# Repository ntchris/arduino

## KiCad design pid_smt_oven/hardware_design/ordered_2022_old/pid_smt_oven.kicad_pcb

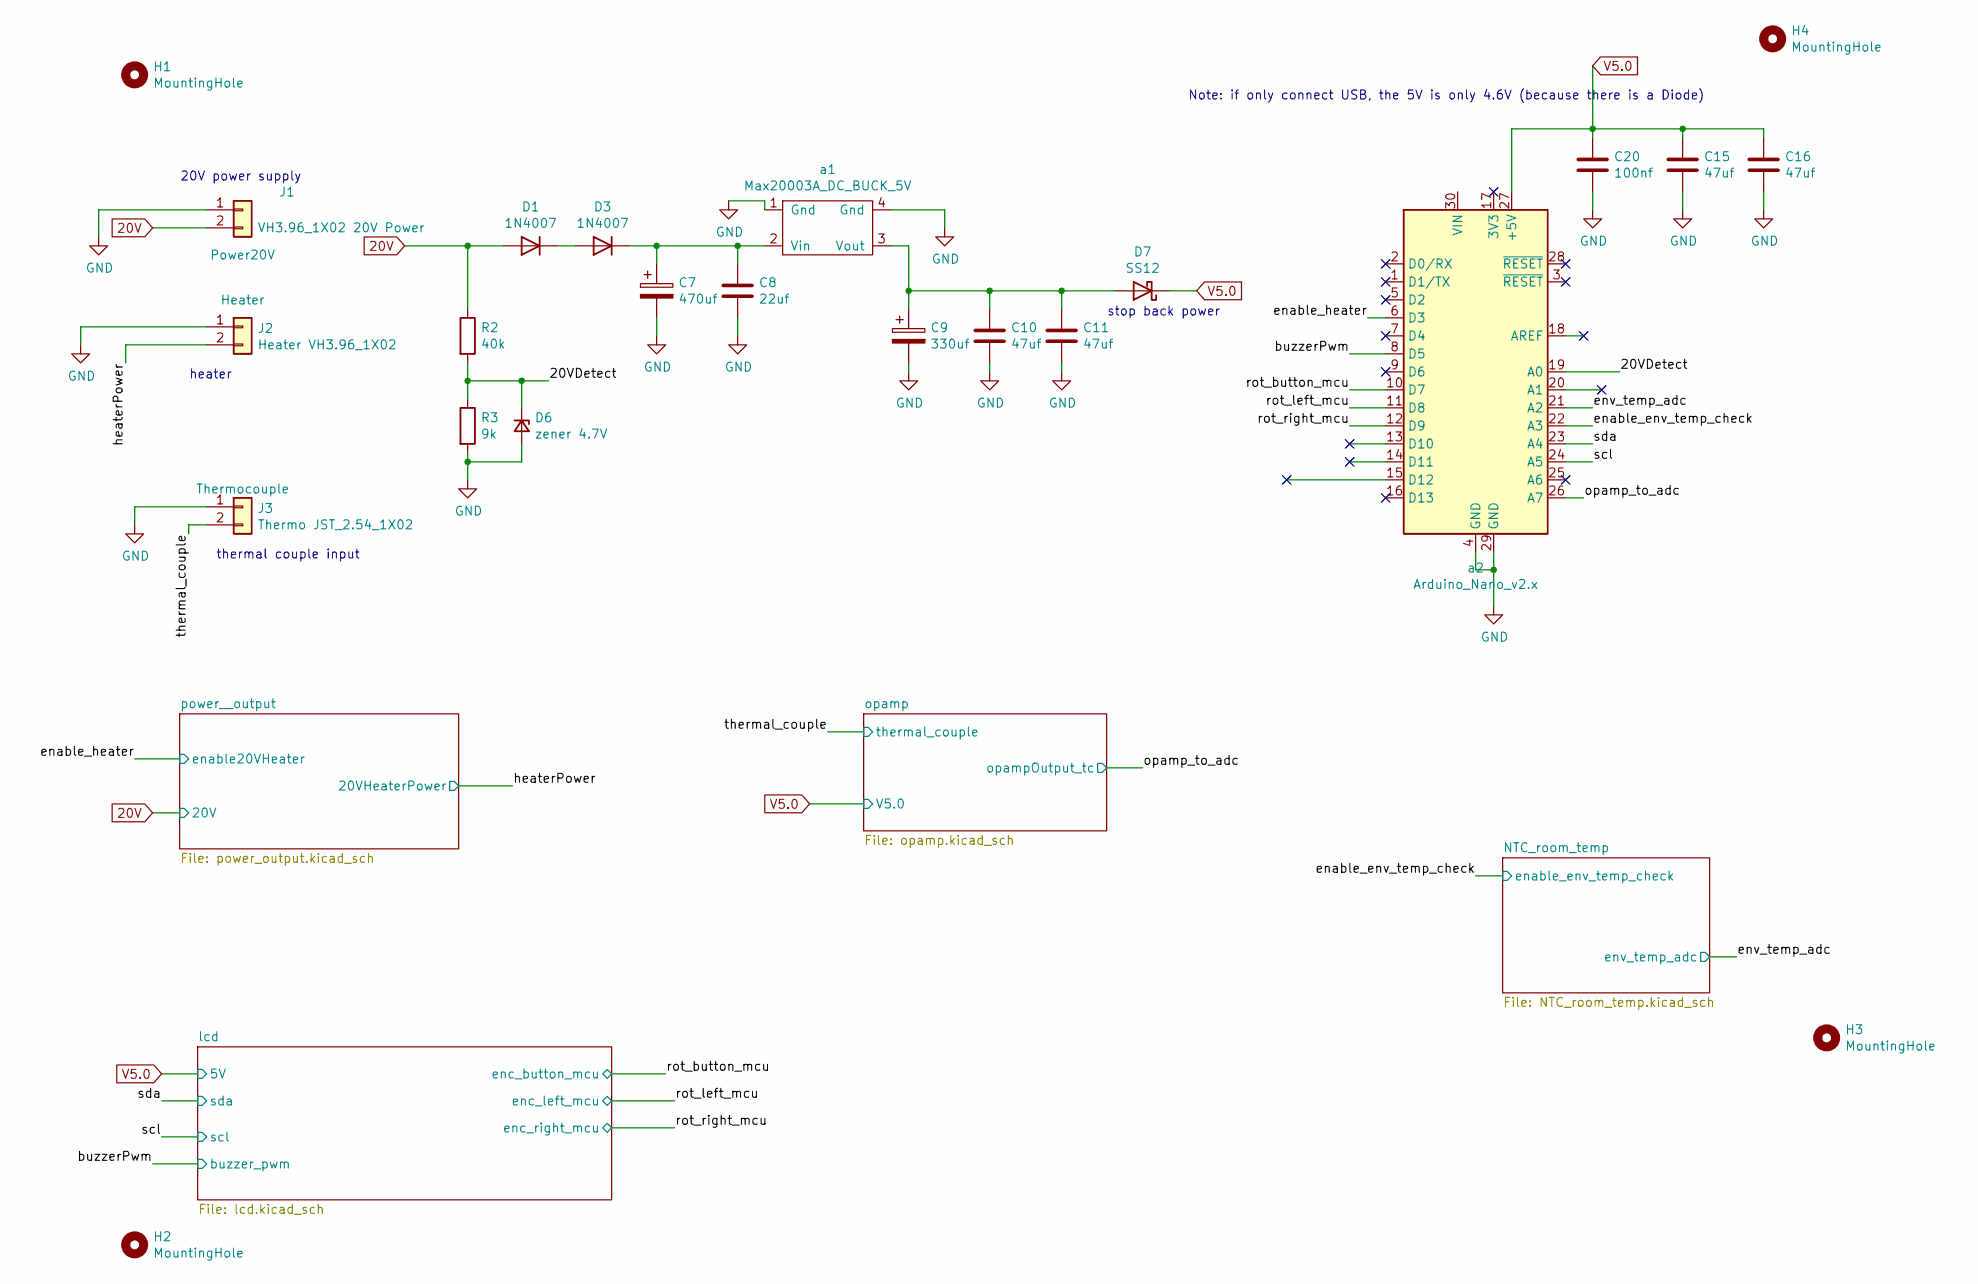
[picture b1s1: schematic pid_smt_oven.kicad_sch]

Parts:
C7: 470uf; CP_Radial_D8.0mm_P3.80mm
C8: 22uf; C_1206_3216Metric_Pad1.33x1.80mm_HandSolder
C9: 330uf; CP_EIA-7343-20_Kemet-V_Pad2.25x2.55mm_HandSolder
C10, C11, C15, C16: 47uf; R_C_0805_2012Metric_Pad1.20x1.50mm_HandSolder
C20: 100nf; R_C_0805_2012Metric_Pad1.20x1.50mm_HandSolder
D1, D3: 1N4007; D_SMA_Handsoldering
D6: zener 4.7V; D_MiniMELF_Handsoldering_Zener
D7: SS12; D_SMA_Handsoldering
H1, H2, H3, H4: MountingHole; MountingHole_2.0mm
J1: VH3.96_1X02 20V Power; JST_VH_B2P-VH-B_1x02_P3.96mm_Vertical
J2: Heater VH3.96_1X02; JST_VH_B2P-VH-B_1x02_P3.96mm_Vertical
J3: Thermo JST_2.54_1X02; Molex_KK-254_AE-6410-02A_1x02_P2.54mm_Vertical
R2: 40k; R_C_0805_2012Metric_Pad1.20x1.50mm_HandSolder
R3: 9k; R_C_0805_2012Metric_Pad1.20x1.50mm_HandSolder
a1: Max20003A_DC_BUCK_5V; MAX20003A_dc_buck_module
a2: Arduino_Nano_v2.x; Arduino_Nano_order

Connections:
20V: D1.2 (A), J1.2, R2.1; also elsewhere on the board
/20VDetect: D6.1 (K), R2.2, R3.1, a2.19 (A0)
/buzzerPwm: a2.8 (D5); also elsewhere on the board
/enable_env_temp_check: a2.22 (A3); also elsewhere on the board
/enable_heater: a2.6 (D3); also elsewhere on the board
/env_temp_adc: a2.21 (A2); also elsewhere on the board
/heaterPower: J2.2; also elsewhere on the board
/opamp_to_adc: a2.26 (A7); also elsewhere on the board
/relayTrigger: a2.15 (D12)
/rot_button_mcu: a2.10 (D7); also elsewhere on the board
/rot_left_mcu: a2.11 (D8); also elsewhere on the board
/rot_right_mcu: a2.12 (D9); also elsewhere on the board
/scl: a2.24 (A5); also elsewhere on the board
/sda: a2.23 (A4); also elsewhere on the board
/thermal_couple: J3.2; also elsewhere on the board
GND: C7.2, C8.2, C9.2, C10.2, C11.2, C15.2, C16.2, C20.2, D6.2 (A), J1.1, J2.1, J3.1, R3.2, a1.1 (Gnd), a1.4 (Gnd), a2.4 (GND), a2.29 (GND); also elsewhere on the board
unnamed: C7.1, C8.1, D3.1 (K), a1.2 (Vin)
unnamed: C9.1, C10.1, C11.1, D7.2 (A), a1.3 (Vout)
unnamed: D1.1 (K), D3.2 (A)
V5.0: C15.1, C16.1, C20.1, D7.1 (K), a2.27 (+5V); also elsewhere on the board

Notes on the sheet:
heater
stop back power
20V power supply
thermal couple input
Note: if only connect USB, the 5V is only 4.6V (because there is a Diode)

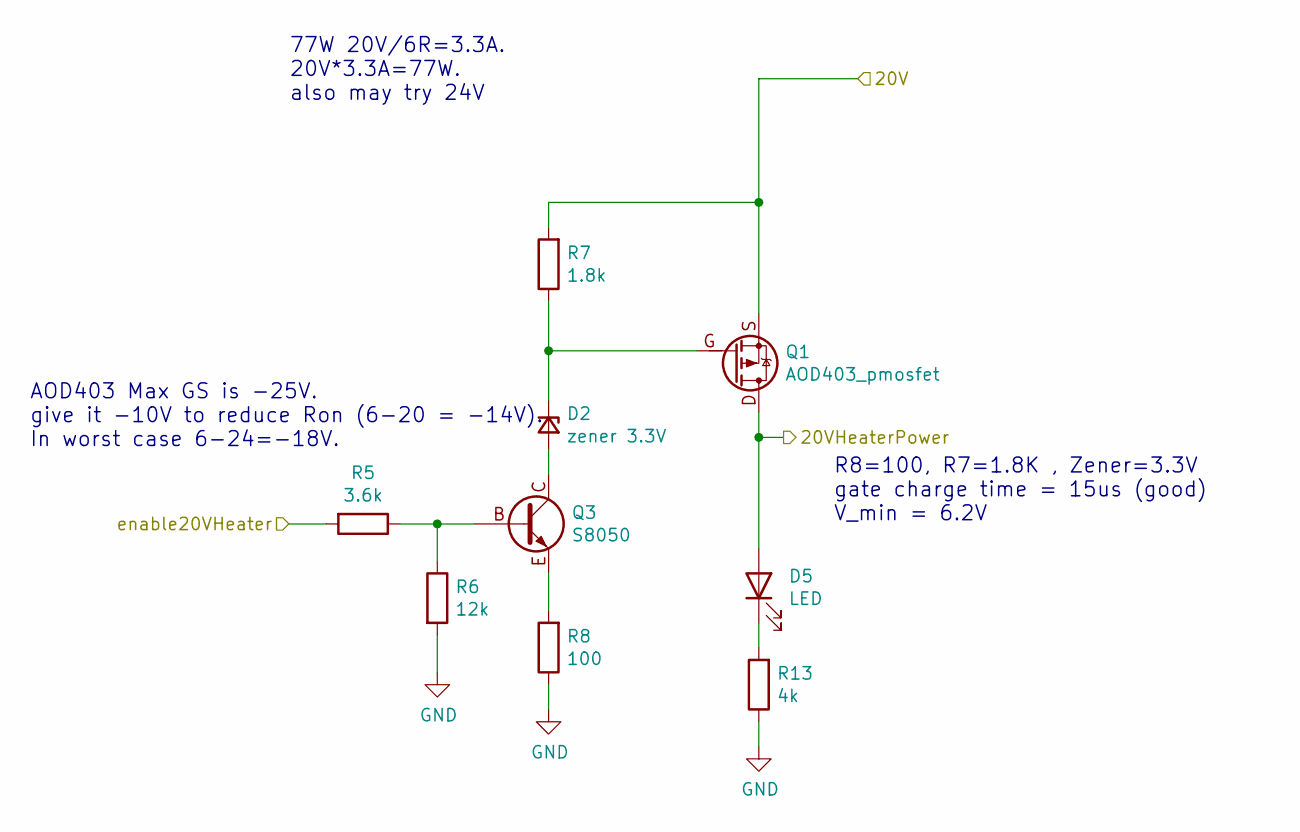
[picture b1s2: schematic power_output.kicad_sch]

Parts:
D2: zener 3.3V; D_MiniMELF_Handsoldering_Zener
D5: LED; LED_D3.0mm
Q1: AOD403_pmosfet; TO-252-2
Q3: S8050; SOT-23_PNP_NPN
R5: 3.6k; R_C_0805_2012Metric_Pad1.20x1.50mm_HandSolder
R6: 12k; R_C_0805_2012Metric_Pad1.20x1.50mm_HandSolder
R7: 1.8k; R_C_0805_2012Metric_Pad1.20x1.50mm_HandSolder
R8: 100; R_C_0805_2012Metric_Pad1.20x1.50mm_HandSolder
R13: 4k; R_C_0805_2012Metric_Pad1.20x1.50mm_HandSolder

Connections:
20V: Q1.S, R7.2; also elsewhere on the board
/enable_heater: R5.2; also elsewhere on the board
/heaterPower: D5.A, Q1.D; also elsewhere on the board
GND: R6.2, R8.1, R13.1; also elsewhere on the board
unnamed: D2.1 (K), Q1.G, R7.1
unnamed: D2.2 (A), Q3.C
unnamed: D5.K, R13.2
unnamed: Q3.B, R5.1, R6.1
unnamed: Q3.E, R8.2

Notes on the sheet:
77W 20V/6R=3.3A. 20V*3.3A=77W. also may try 24V
R8=100, R7=1.8K , Zener=3.3V gate charge time = 15us (good) V_min = 6.2V
AOD403 Max GS is -25V. give it -10V to reduce Ron (6-20 = -14V). In worst case 6-24=-18V.

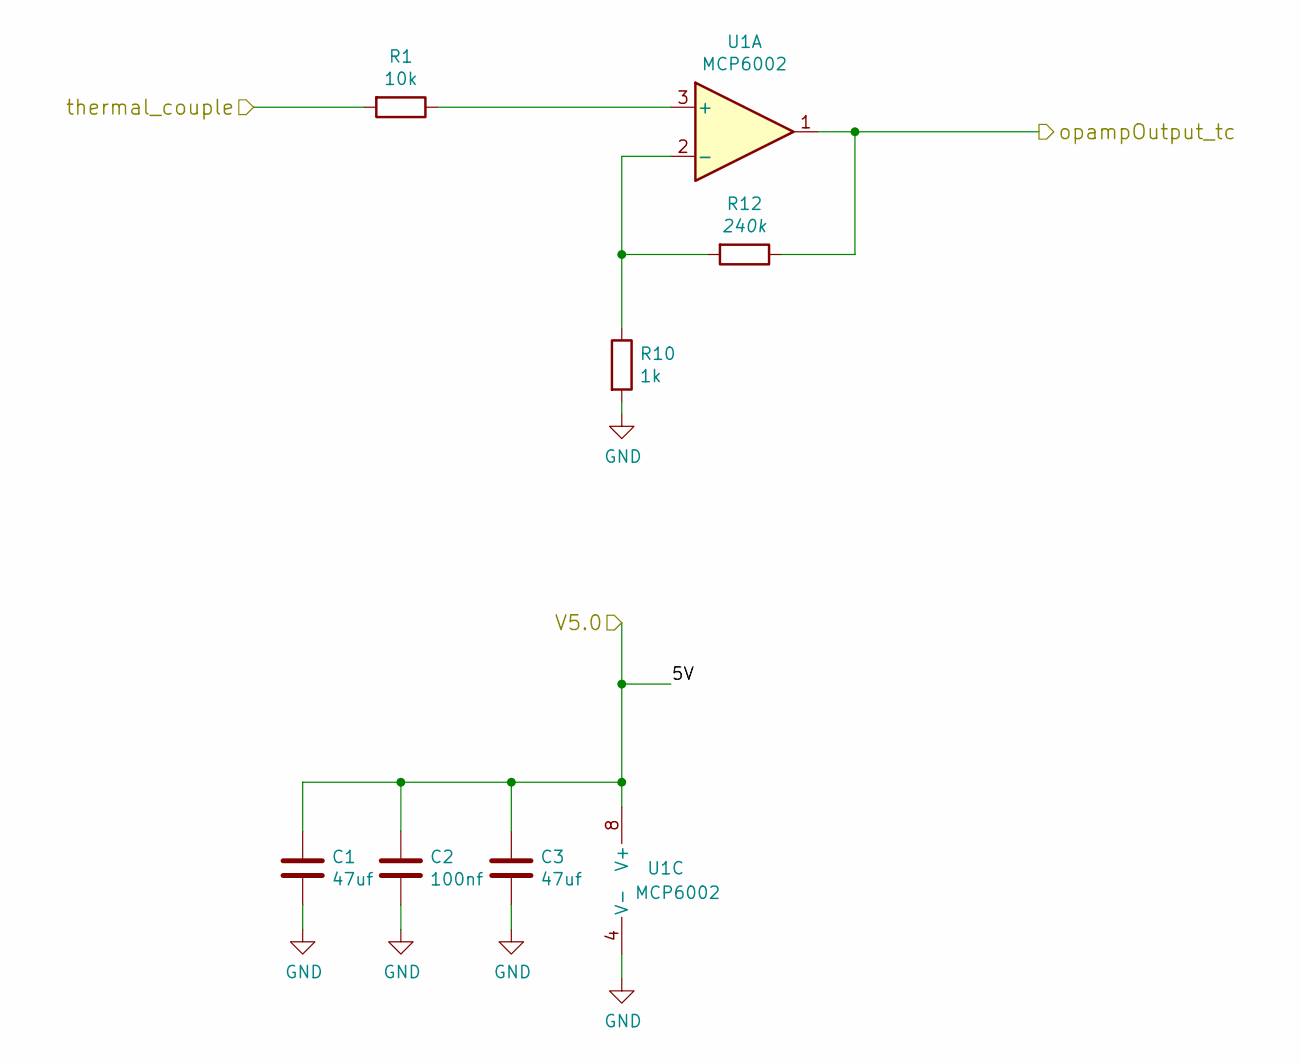
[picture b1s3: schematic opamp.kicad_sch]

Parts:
C1, C3: 47uf; R_C_0805_2012Metric_Pad1.20x1.50mm_HandSolder
C2: 100nf; R_C_0805_2012Metric_Pad1.20x1.50mm_HandSolder
R1: 10k; R_C_0805_2012Metric_Pad1.20x1.50mm_HandSolder
R10: 1k; R_1206_3216Metric_Pad1.30x1.75mm_HandSolder
R12: 240k; R_C_0805_2012Metric_Pad1.20x1.50mm_HandSolder
U1: MCP6002; SO-8_3.9x4.9mm_P1.27mm

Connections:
/opamp_to_adc: R12.1, U1.1; also elsewhere on the board
/thermal_couple: R1.2; also elsewhere on the board
GND: C1.2, C2.2, C3.2, R10.2, U1.4 (V-); also elsewhere on the board
unnamed: R1.1, U1.3 (+)
unnamed: R10.1, R12.2, U1.2 (-)
V5.0: C1.1, C2.1, C3.1, U1.8 (V+); also elsewhere on the board

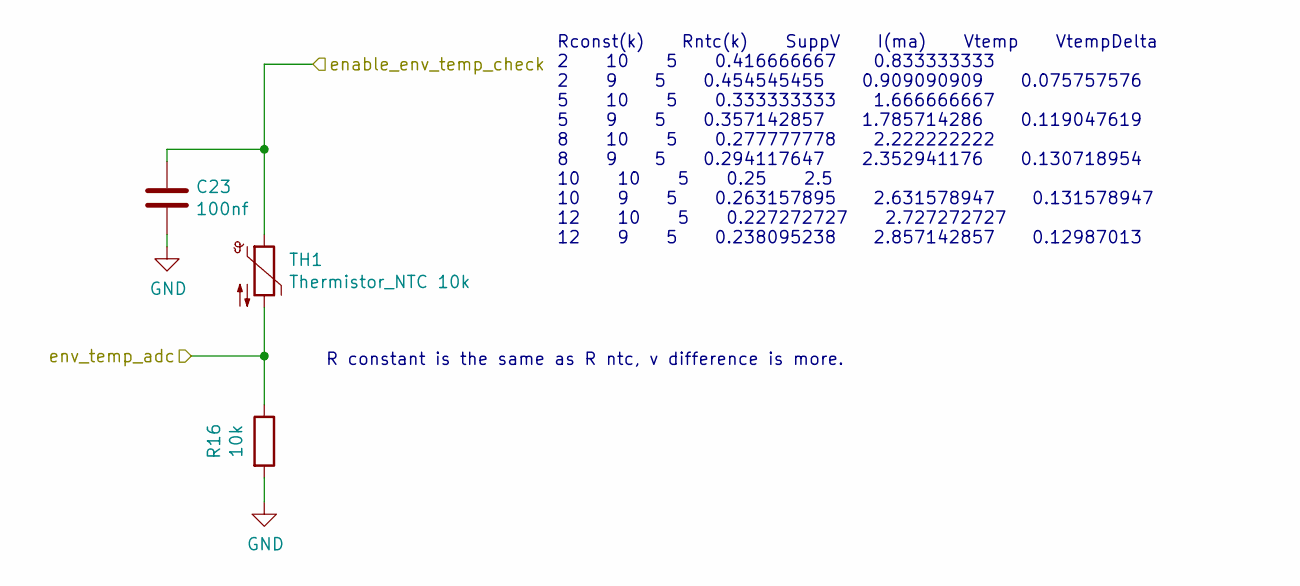
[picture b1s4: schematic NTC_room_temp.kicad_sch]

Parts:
C23: 100nf; R_C_0805_2012Metric_Pad1.20x1.50mm_HandSolder
R16: 10k; R_C_0805_2012Metric_Pad1.20x1.50mm_HandSolder
TH1: Thermistor_NTC 10k; R_Axial_DIN0207_L6.3mm_D2.5mm_P15.24mm_Horizontal

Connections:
/enable_env_temp_check: C23.1, TH1.1; also elsewhere on the board
/env_temp_adc: R16.1, TH1.2; also elsewhere on the board
GND: C23.2, R16.2; also elsewhere on the board

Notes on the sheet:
R constant is the same as R ntc, v difference is more.
Rconst(k) Rntc(k) SuppV I(ma) Vtemp VtempDelta 2 10 5 0.416666667 0.833333333 2 9 5 0.454545455 0.909090909 0.075757576 5 10 5 0.333333333 1.666666667 5 9 5 0.357142857 1.785714286 0.119047619 8 10 5 0.277777778 2.222222222 8 9 5 0.294117647 2.352941176 0.130718954 10 10 5 0.25 2.5 10 9 5 0.2631578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

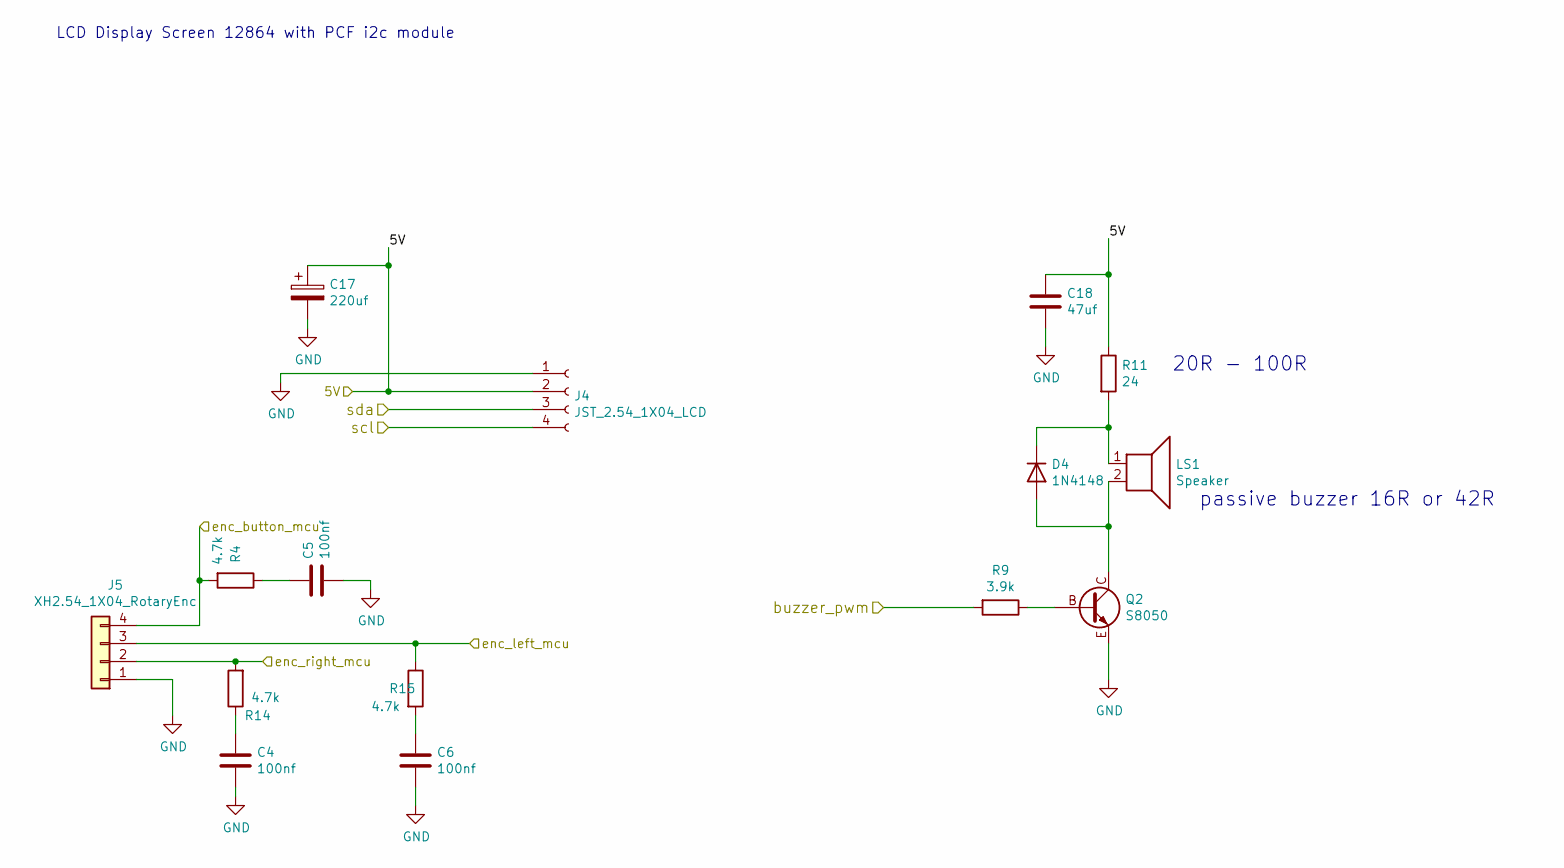
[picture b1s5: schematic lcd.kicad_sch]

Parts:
C4, C5, C6: 100nf; R_C_0805_2012Metric_Pad1.20x1.50mm_HandSolder
C17: 220uf; CP_EIA-7343-20_Kemet-V_Pad2.25x2.55mm_HandSolder
C18: 47uf; R_C_0805_2012Metric_Pad1.20x1.50mm_HandSolder
D4: 1N4148; D_MiniMELF_Handsoldering_Zener
J4: JST_2.54_1X04_LCD; Molex_KK-254_AE-6410-04A_1x04_P2.54mm_Vertical
J5: XH2.54_1X04_RotaryEnc; JST_XH_1x04_P2.54mm_Vertical
LS1: Speaker; Buzzer_9x4.2
Q2: S8050; SOT-23_PNP_NPN
R4, R14, R15: 4.7k; R_C_0805_2012Metric_Pad1.20x1.50mm_HandSolder
R9: 3.9k; R_C_0805_2012Metric_Pad1.20x1.50mm_HandSolder
R11: 24; R_C_0805_2012Metric_Pad1.20x1.50mm_HandSolder

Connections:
/buzzerPwm: R9.2; also elsewhere on the board
/rot_button_mcu: J5.4, R4.2; also elsewhere on the board
/rot_left_mcu: J5.3, R15.1; also elsewhere on the board
/rot_right_mcu: J5.2, R14.2; also elsewhere on the board
/scl: J4.4; also elsewhere on the board
/sda: J4.3; also elsewhere on the board
GND: C4.2, C5.2, C6.2, C17.2, C18.2, J4.1, J5.1, Q2.E; also elsewhere on the board
unnamed: C4.1, R14.1
unnamed: C5.1, R4.1
unnamed: C6.1, R15.2
unnamed: D4.1 (K), LS1.1, R11.2
unnamed: D4.2 (A), LS1.2, Q2.C
unnamed: Q2.B, R9.1
V5.0: C17.1, C18.1, J4.2, R11.1; also elsewhere on the board

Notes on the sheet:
passive buzzer 16R or 42R
LCD Display Screen 12864 with PCF i2c module
20R - 100R

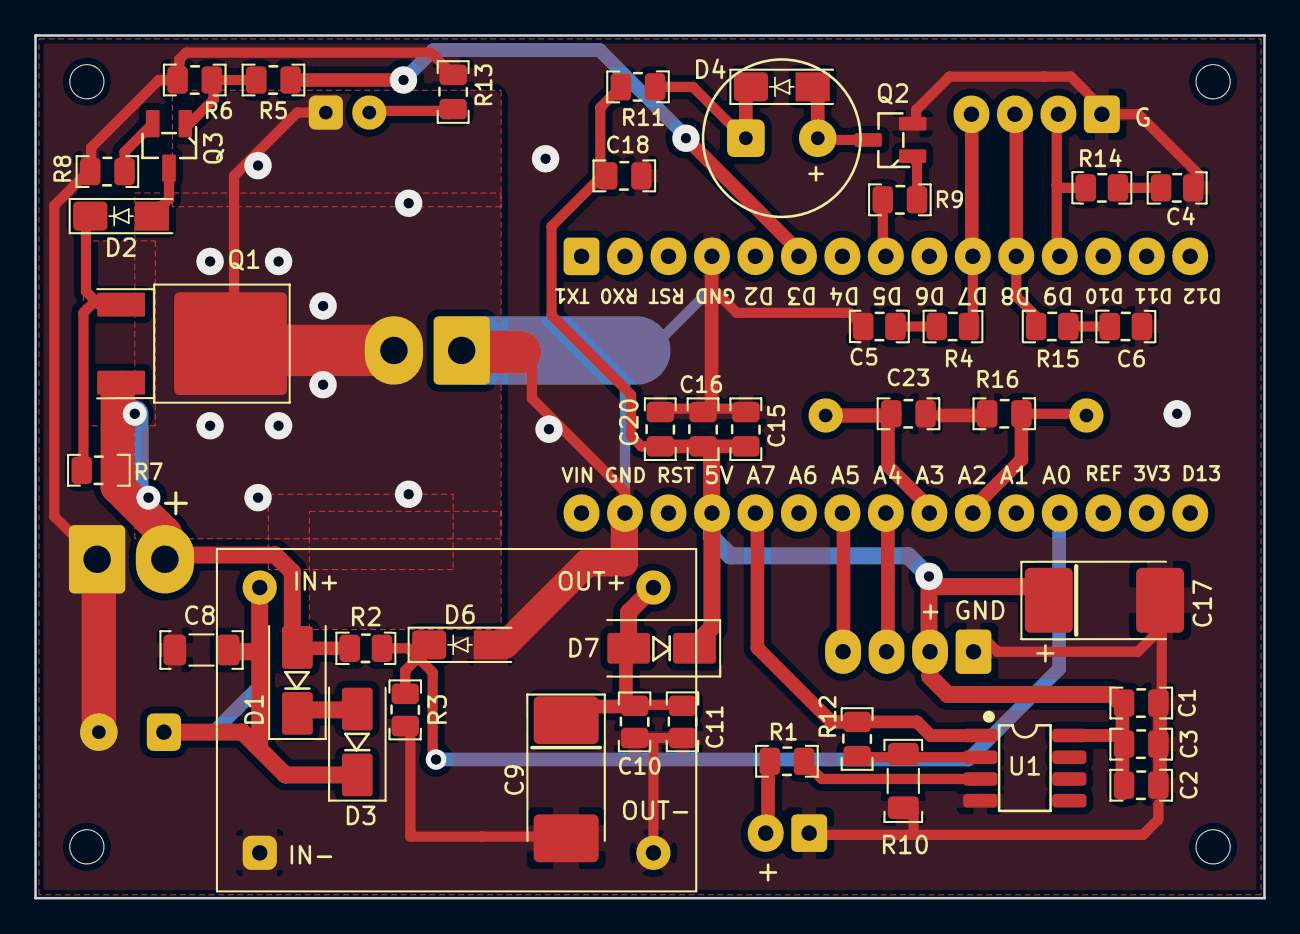
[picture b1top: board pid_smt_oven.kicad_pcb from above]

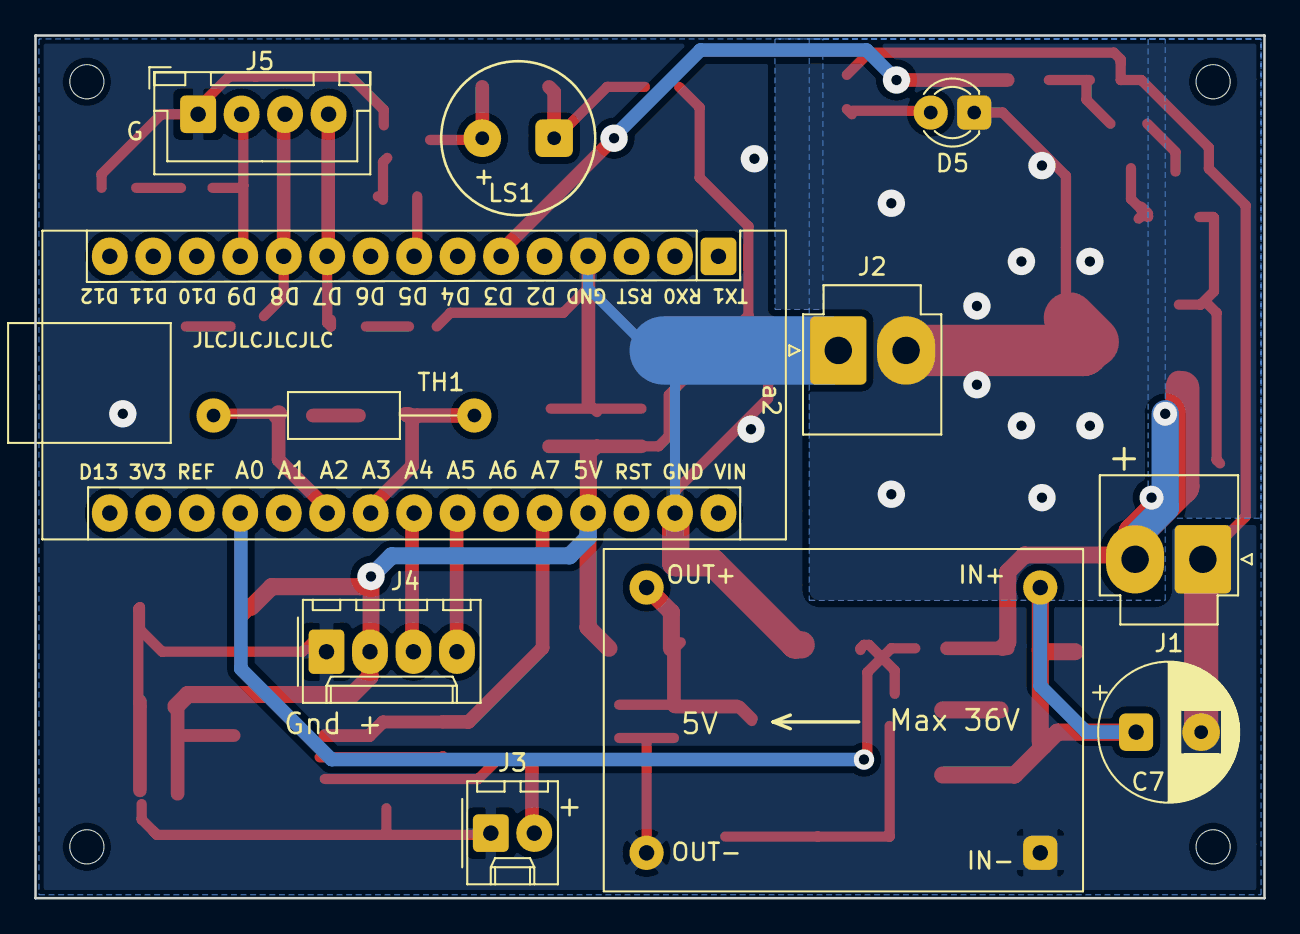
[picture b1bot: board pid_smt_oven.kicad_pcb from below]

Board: 2 copper layers, 71.8 x 50.4 mm, 57 parts (11 on the bottom side), 32 nets.

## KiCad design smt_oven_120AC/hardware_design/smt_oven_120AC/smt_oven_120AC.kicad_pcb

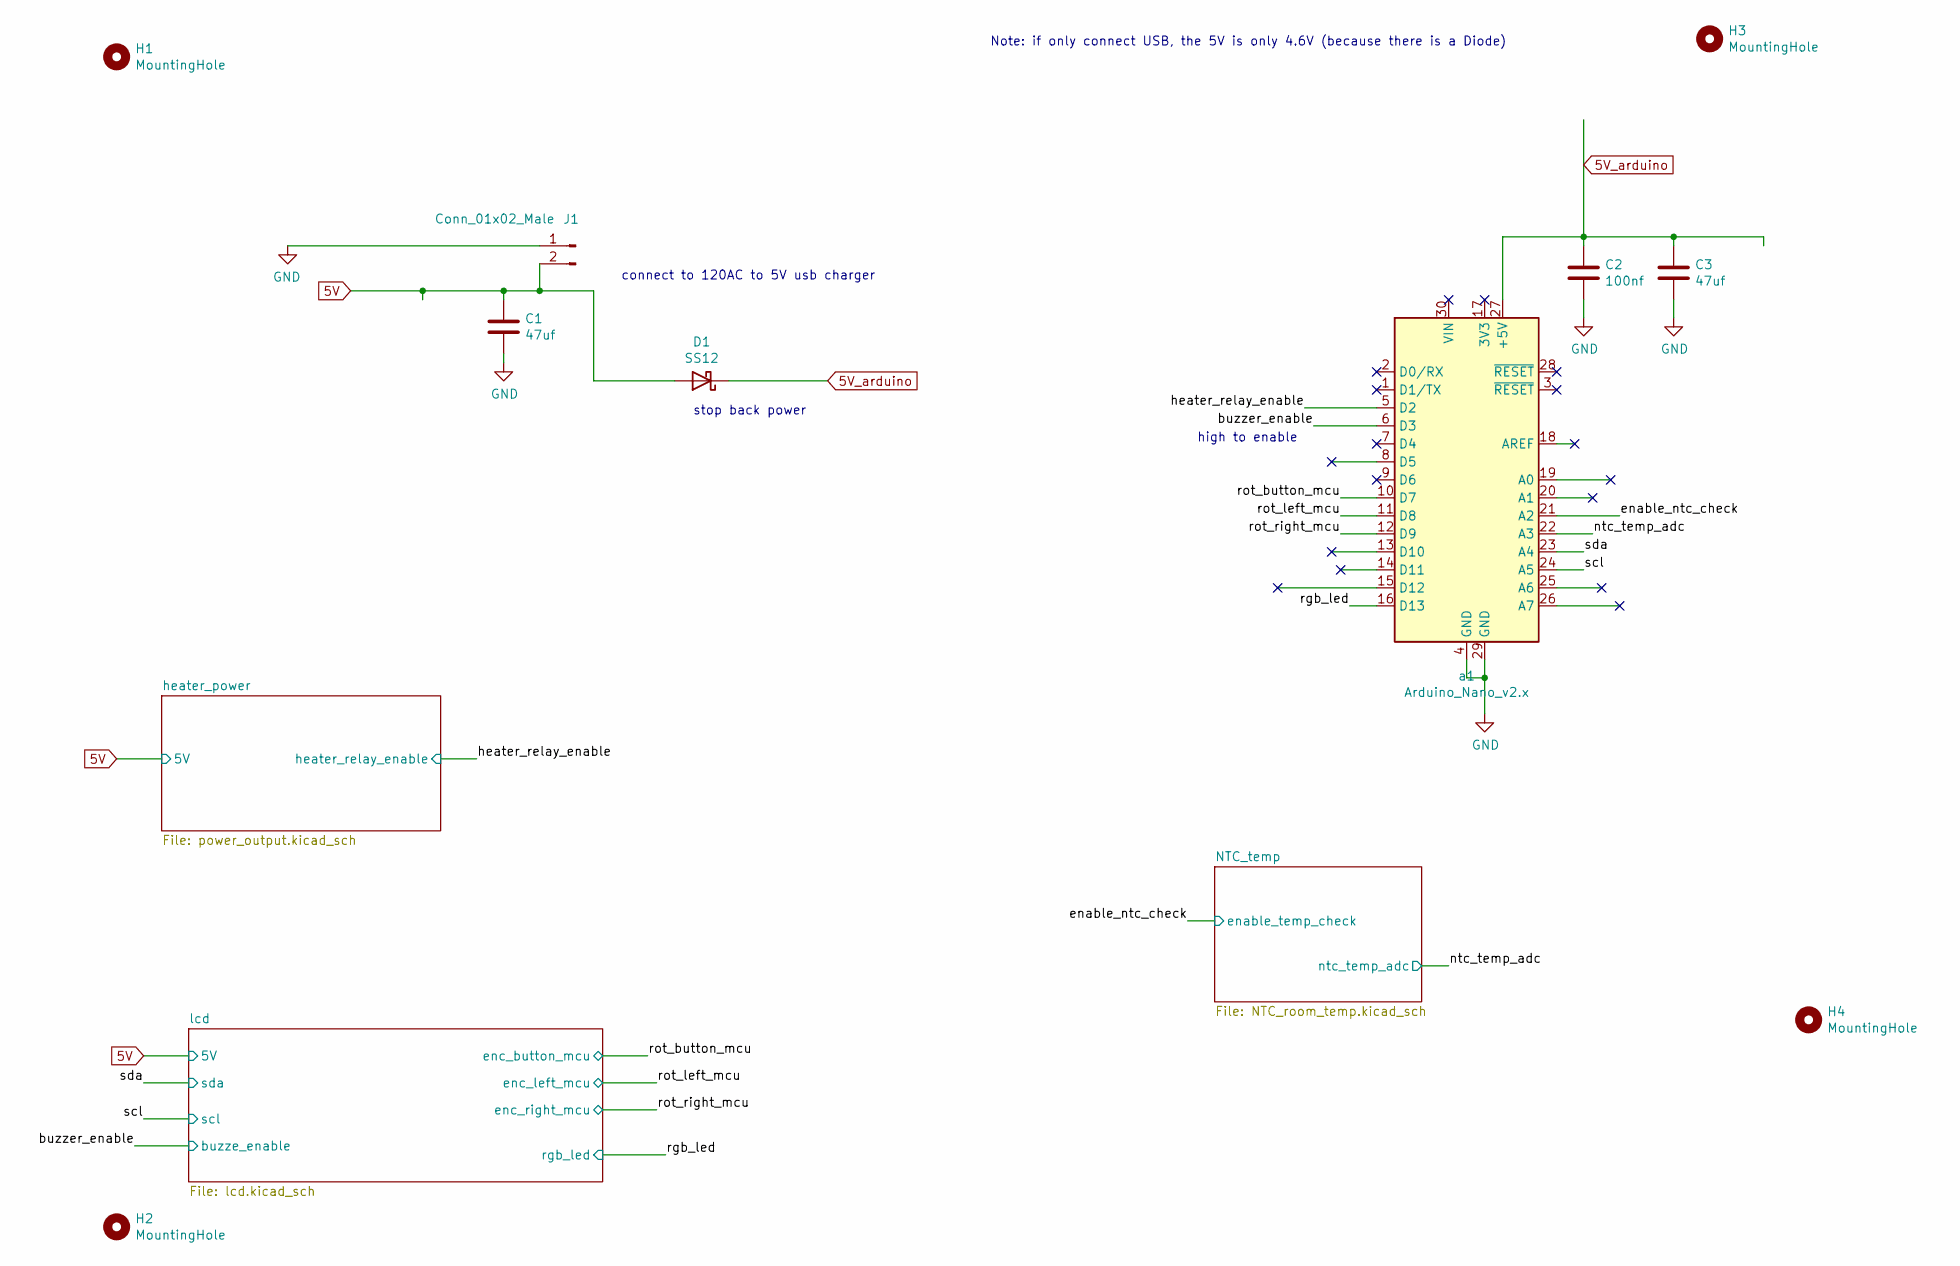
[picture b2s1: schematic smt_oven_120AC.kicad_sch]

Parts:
C1, C3: 47uf; R_C_0805_2012Metric_Pad1.20x1.50mm_HandSolder
C2: 100nf; R_C_0805_2012Metric_Pad1.20x1.50mm_HandSolder
D1: SS12; D_SMA_Handsoldering
H1, H2, H3, H4: MountingHole; MountingHole_2.0mm
J1: Conn_01x02_Male; Molex_KK-254_1x02_P2.54mm_Vertical_order
a1: Arduino_Nano_v2.x; Arduino_Nano_order

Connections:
5V: C1.1, D1.2 (A), J1.2; also elsewhere on the board
5V_arduino: C2.1, C3.1, D1.1 (K), a1.27 (+5V)
/buzzer_enable: a1.6 (D3); also elsewhere on the board
/enable_ntc_check: a1.21 (A2); also elsewhere on the board
/heater_relay_enable: a1.5 (D2); also elsewhere on the board
/ntc_temp_adc: a1.22 (A3); also elsewhere on the board
/rgb_led: a1.16 (D13); also elsewhere on the board
/rot_button_mcu: a1.10 (D7); also elsewhere on the board
/rot_left_mcu: a1.11 (D8); also elsewhere on the board
/rot_right_mcu: a1.12 (D9); also elsewhere on the board
/scl: a1.24 (A5); also elsewhere on the board
/sda: a1.23 (A4); also elsewhere on the board
GND: C1.2, C2.2, C3.2, J1.1, a1.4 (GND), a1.29 (GND); also elsewhere on the board

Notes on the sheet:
connect to 120AC to 5V usb charger
stop back power
high to enable
Note: if only connect USB, the 5V is only 4.6V (because there is a Diode)

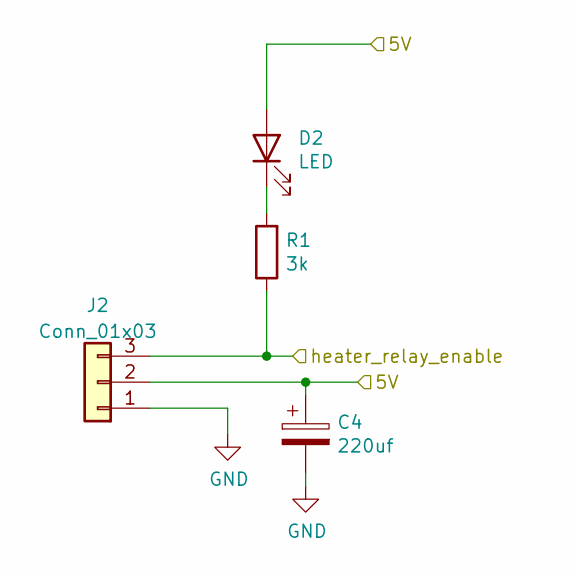
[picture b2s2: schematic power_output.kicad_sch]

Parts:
C4: 220uf; CP_EIA-7343-20_Kemet-V_Pad2.25x2.55mm_HandSolder
D2: LED; LED_D3.0mm
J2: Conn_01x03; Molex_KK-254_AE-6410-03A_1x03_P2.54mm_Vertical
R1: 3k; R_C_0805_2012Metric_Pad1.20x1.50mm_HandSolder

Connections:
5V: C4.1, D2.A, J2.2; also elsewhere on the board
/heater_relay_enable: J2.3, R1.1; also elsewhere on the board
GND: C4.2, J2.1; also elsewhere on the board
unnamed: D2.K, R1.2

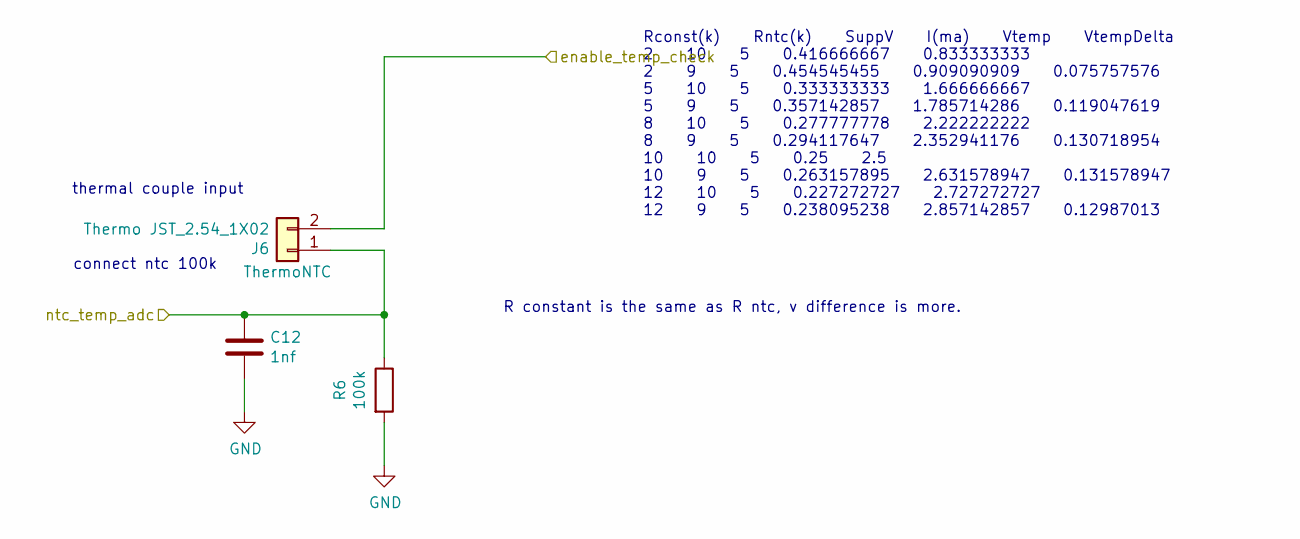
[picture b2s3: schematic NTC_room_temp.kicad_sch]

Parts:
C12: 1nf; R_C_0805_2012Metric_Pad1.20x1.50mm_HandSolder
J6: Thermo JST_2.54_1X02; Molex_KK-254_1x02_P2.54mm_Vertical_order
R6: 100k; R_C_0805_2012Metric_Pad1.20x1.50mm_HandSolder

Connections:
/enable_ntc_check: J6.2; also elsewhere on the board
/ntc_temp_adc: C12.1, J6.1, R6.1; also elsewhere on the board
GND: C12.2, R6.2; also elsewhere on the board

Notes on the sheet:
R constant is the same as R ntc, v difference is more.
Rconst(k) Rntc(k) SuppV I(ma) Vtemp VtempDelta 2 10 5 0.416666667 0.833333333 2 9 5 0.454545455 0.909090909 0.075757576 5 10 5 0.333333333 1.666666667 5 9 5 0.357142857 1.785714286 0.119047619 8 10 5 0.277777778 2.222222222 8 9 5 0.294117647 2.352941176 0.130718954 10 10 5 0.25 2.5 10 9 5 0.2631578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
connect ntc 100k
thermal couple input

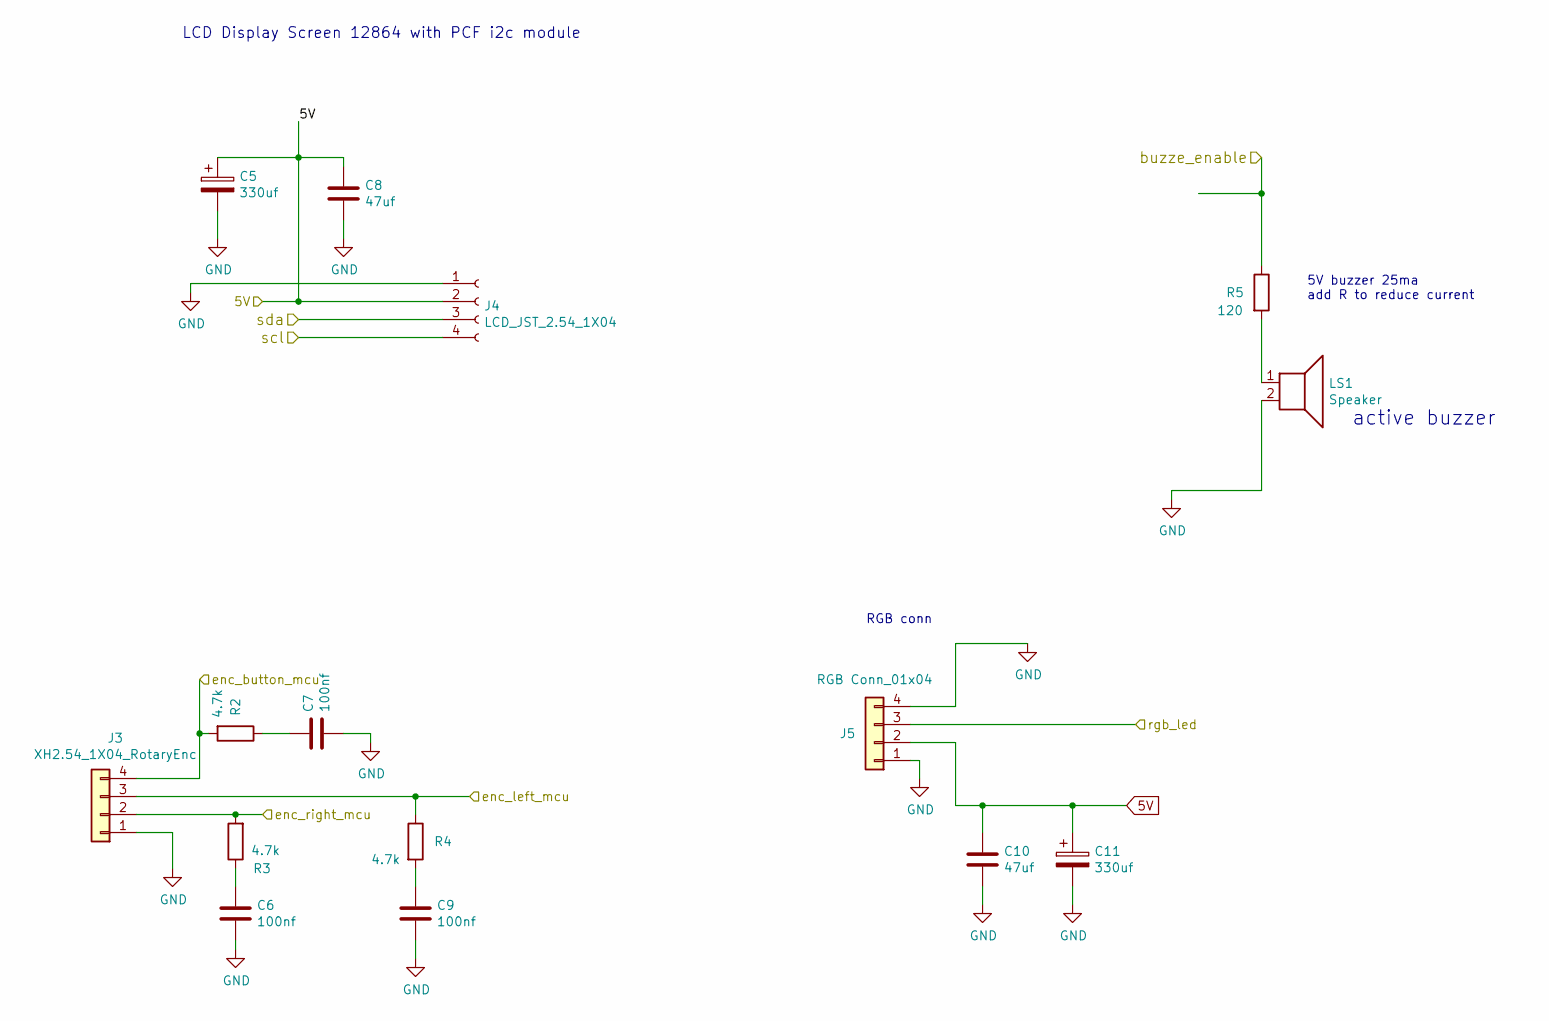
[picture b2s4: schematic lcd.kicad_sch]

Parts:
C5, C11: 330uf; CP_EIA-7343-20_Kemet-V_Pad2.25x2.55mm_HandSolder
C6, C7, C9: 100nf; R_C_0805_2012Metric_Pad1.20x1.50mm_HandSolder
C8, C10: 47uf; R_C_0805_2012Metric_Pad1.20x1.50mm_HandSolder
J3: XH2.54_1X04_RotaryEnc; JST_XH_1x04_P2.54mm_Vertical
J4: LCD_JST_2.54_1X04; Molex_KK-254_1x04_P2.54mm_Vertical_order
J5: RGB Conn_01x04; Molex_KK-254_1x04_P2.54mm_Vertical_order
LS1: Speaker; Buzzer_12x9.5RM7.6
R2, R3, R4: 4.7k; R_C_0805_2012Metric_Pad1.20x1.50mm_HandSolder
R5: 120; R_C_0805_2012Metric_Pad1.20x1.50mm_HandSolder

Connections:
5V: C5.1, C8.1, C10.1, C11.1, J4.2, J5.2; also elsewhere on the board
/buzzer_enable: R5.1; also elsewhere on the board
/rgb_led: J5.3; also elsewhere on the board
/rot_button_mcu: J3.4, R2.2; also elsewhere on the board
/rot_left_mcu: J3.3, R4.1; also elsewhere on the board
/rot_right_mcu: J3.2, R3.2; also elsewhere on the board
/scl: J4.4; also elsewhere on the board
/sda: J4.3; also elsewhere on the board
GND: C5.2, C6.2, C7.2, C8.2, C9.2, C10.2, C11.2, J3.1, J4.1, J5.1, J5.4, LS1.2; also elsewhere on the board
unnamed: C6.1, R3.1
unnamed: C7.1, R2.1
unnamed: C9.1, R4.2
unnamed: LS1.1, R5.2

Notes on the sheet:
active buzzer
RGB conn
5V buzzer 25ma add R to reduce current
LCD Display Screen 12864 with PCF i2c module

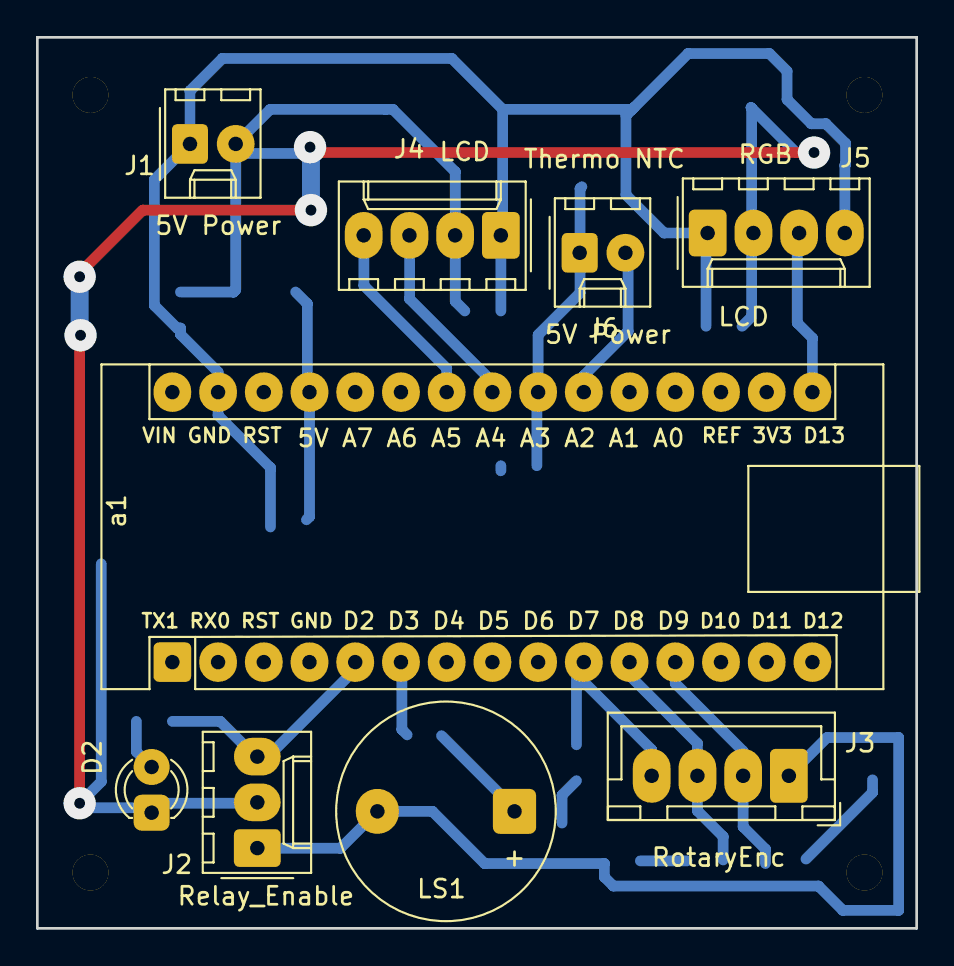
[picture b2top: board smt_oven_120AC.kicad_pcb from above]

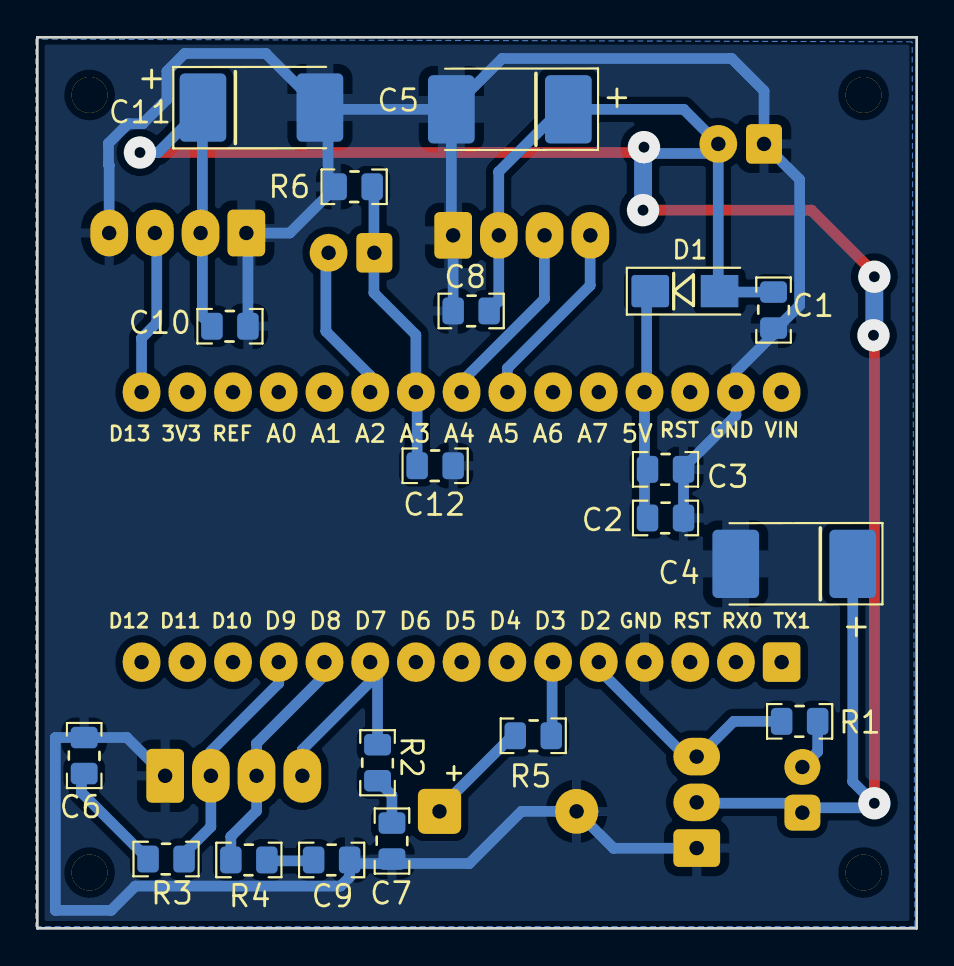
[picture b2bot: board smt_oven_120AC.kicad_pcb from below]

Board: 2 copper layers, 48.9 x 49.5 mm, 32 parts (19 on the bottom side), 18 nets.
